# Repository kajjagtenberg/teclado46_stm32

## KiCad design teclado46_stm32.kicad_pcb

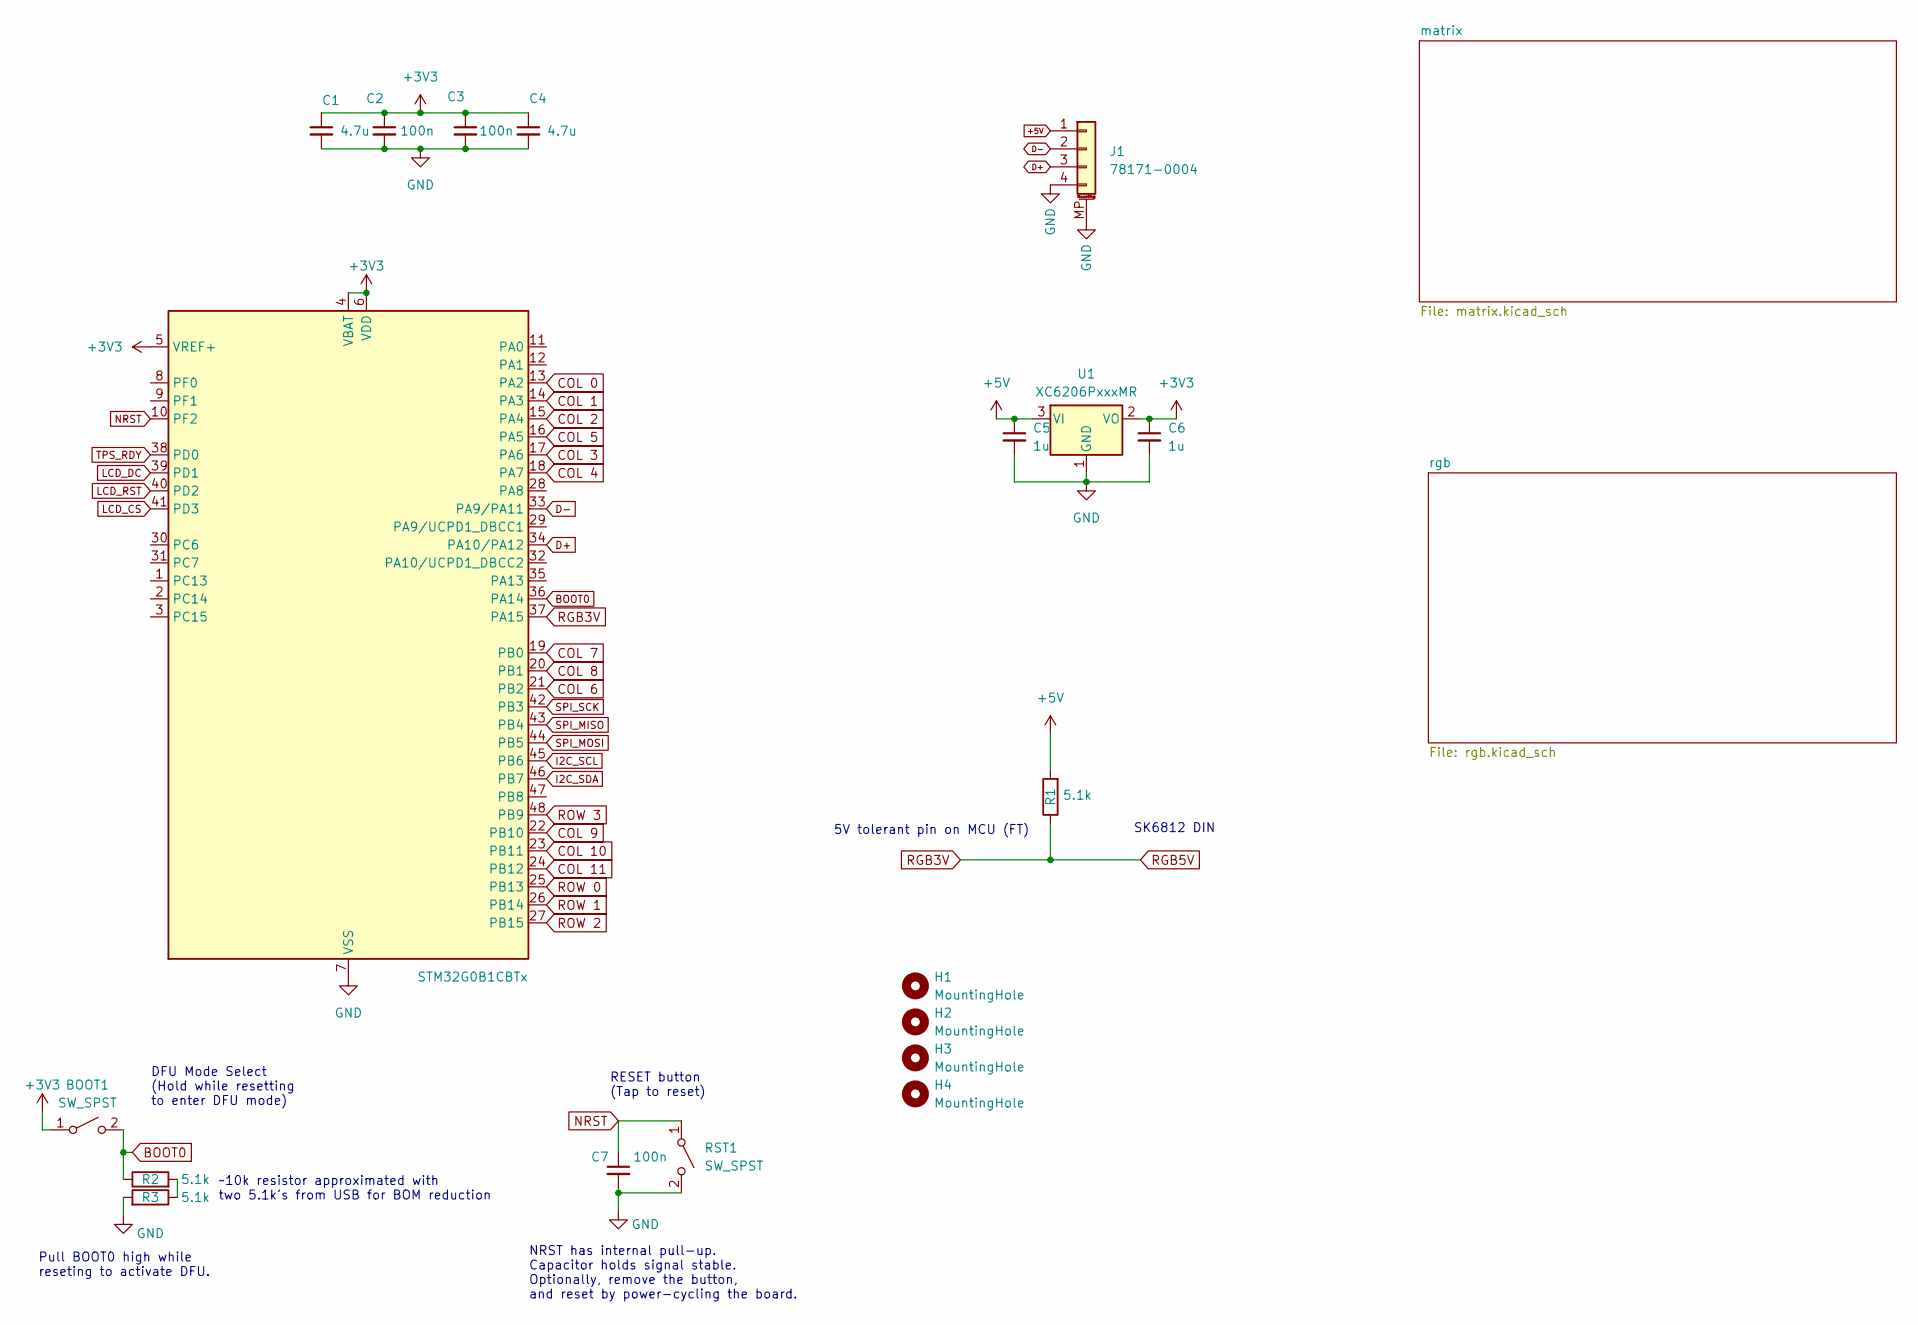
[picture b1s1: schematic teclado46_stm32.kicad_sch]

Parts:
BOOT1: SW_SPST; SW_SPST_TS-1088-xR020; LCSC C720477
C1, C4: 4.7u; C_0402_1005Metric; LCSC C23733
C2, C3, C7: 100n; C_0402_1005Metric; LCSC C1525
C5, C6: 1u; C_0402_1005Metric; LCSC C52923
H1, H2, H3, H4: MountingHole; MountingHole_2.2mm_M2
J1: 78171-0004; Molex_Pico-EZmate_78171-0004_1x04-1MP_P1.20mm_Vertical; Manufacturer Part Number 78171-0004; LCSC C588524
R1, R2, R3: 5.1k; R_0402_1005Metric; LCSC C25905
RST1: SW_SPST; SW_SPST_TS-1088-xR020; LCSC C720477
U1: XC6206PxxxMR; SOT-23-3; LCSC C5446
U2: STM32G0B1CBTx; LQFP-48_7x7mm_P0.5mm; LCSC C2847904

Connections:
+3V3: BOOT1.1 (A), C1.1, C2.1, C3.1, C4.1, C6.1, U1.2 (VO), U2.4 (VBAT), U2.5 (VREF+), U2.6 (VDD)
+5V: C5.1, J1.1, R1.2, U1.3 (VI); also elsewhere on the board
BOOT0: BOOT1.2 (B), R2.1, U2.36 (PA14)
COL 0: U2.13 (PA2); also elsewhere on the board
COL 1: U2.14 (PA3); also elsewhere on the board
COL 2: U2.15 (PA4); also elsewhere on the board
COL 3: U2.17 (PA6); also elsewhere on the board
COL 4: U2.18 (PA7); also elsewhere on the board
COL 5: U2.16 (PA5); also elsewhere on the board
COL 6: U2.21 (PB2); also elsewhere on the board
COL 7: U2.19 (PB0); also elsewhere on the board
COL 8: U2.20 (PB1); also elsewhere on the board
COL 9: U2.22 (PB10); also elsewhere on the board
COL 10: U2.23 (PB11); also elsewhere on the board
COL 11: U2.24 (PB12); also elsewhere on the board
D+: J1.3, U2.34 (PA10/PA12)
D-: J1.2, U2.33 (PA9/PA11)
GND: C1.2, C2.2, C3.2, C4.2, C5.2, C6.2, C7.2, J1.4, J1.MP (MountPin), R3.2, RST1.2 (B), U1.1 (GND), U2.7 (VSS); also elsewhere on the board
I2C_SCL: U2.45 (PB6)
I2C_SDA: U2.46 (PB7)
LCD_CS: U2.41 (PD3)
LCD_DC: U2.39 (PD1)
LCD_RST: U2.40 (PD2)
NRST: C7.1, RST1.1 (A), U2.10 (PF2)
unnamed: R2.2, R3.1
RGB3V: R1.1, U2.37 (PA15); also elsewhere on the board
ROW 0: U2.25 (PB13); also elsewhere on the board
ROW 1: U2.26 (PB14); also elsewhere on the board
ROW 2: U2.27 (PB15); also elsewhere on the board
ROW 3: U2.48 (PB9); also elsewhere on the board
SPI_MISO: U2.43 (PB4)
SPI_MOSI: U2.44 (PB5)
SPI_SCK: U2.42 (PB3)
TPS_RDY: U2.38 (PD0)

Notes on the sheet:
SK6812 DIN
Pull BOOT0 high while reseting to activate DFU.
~10k resistor approximated with two 5.1k's from USB for BOM reduction
DFU Mode Select (Hold while resetting to enter DFU mode)
5V tolerant pin on MCU (FT)
NRST has internal pull-up. Capacitor holds signal stable. Optionally, remove the button, and reset by power-cycling the board.
RESET button (Tap to reset)

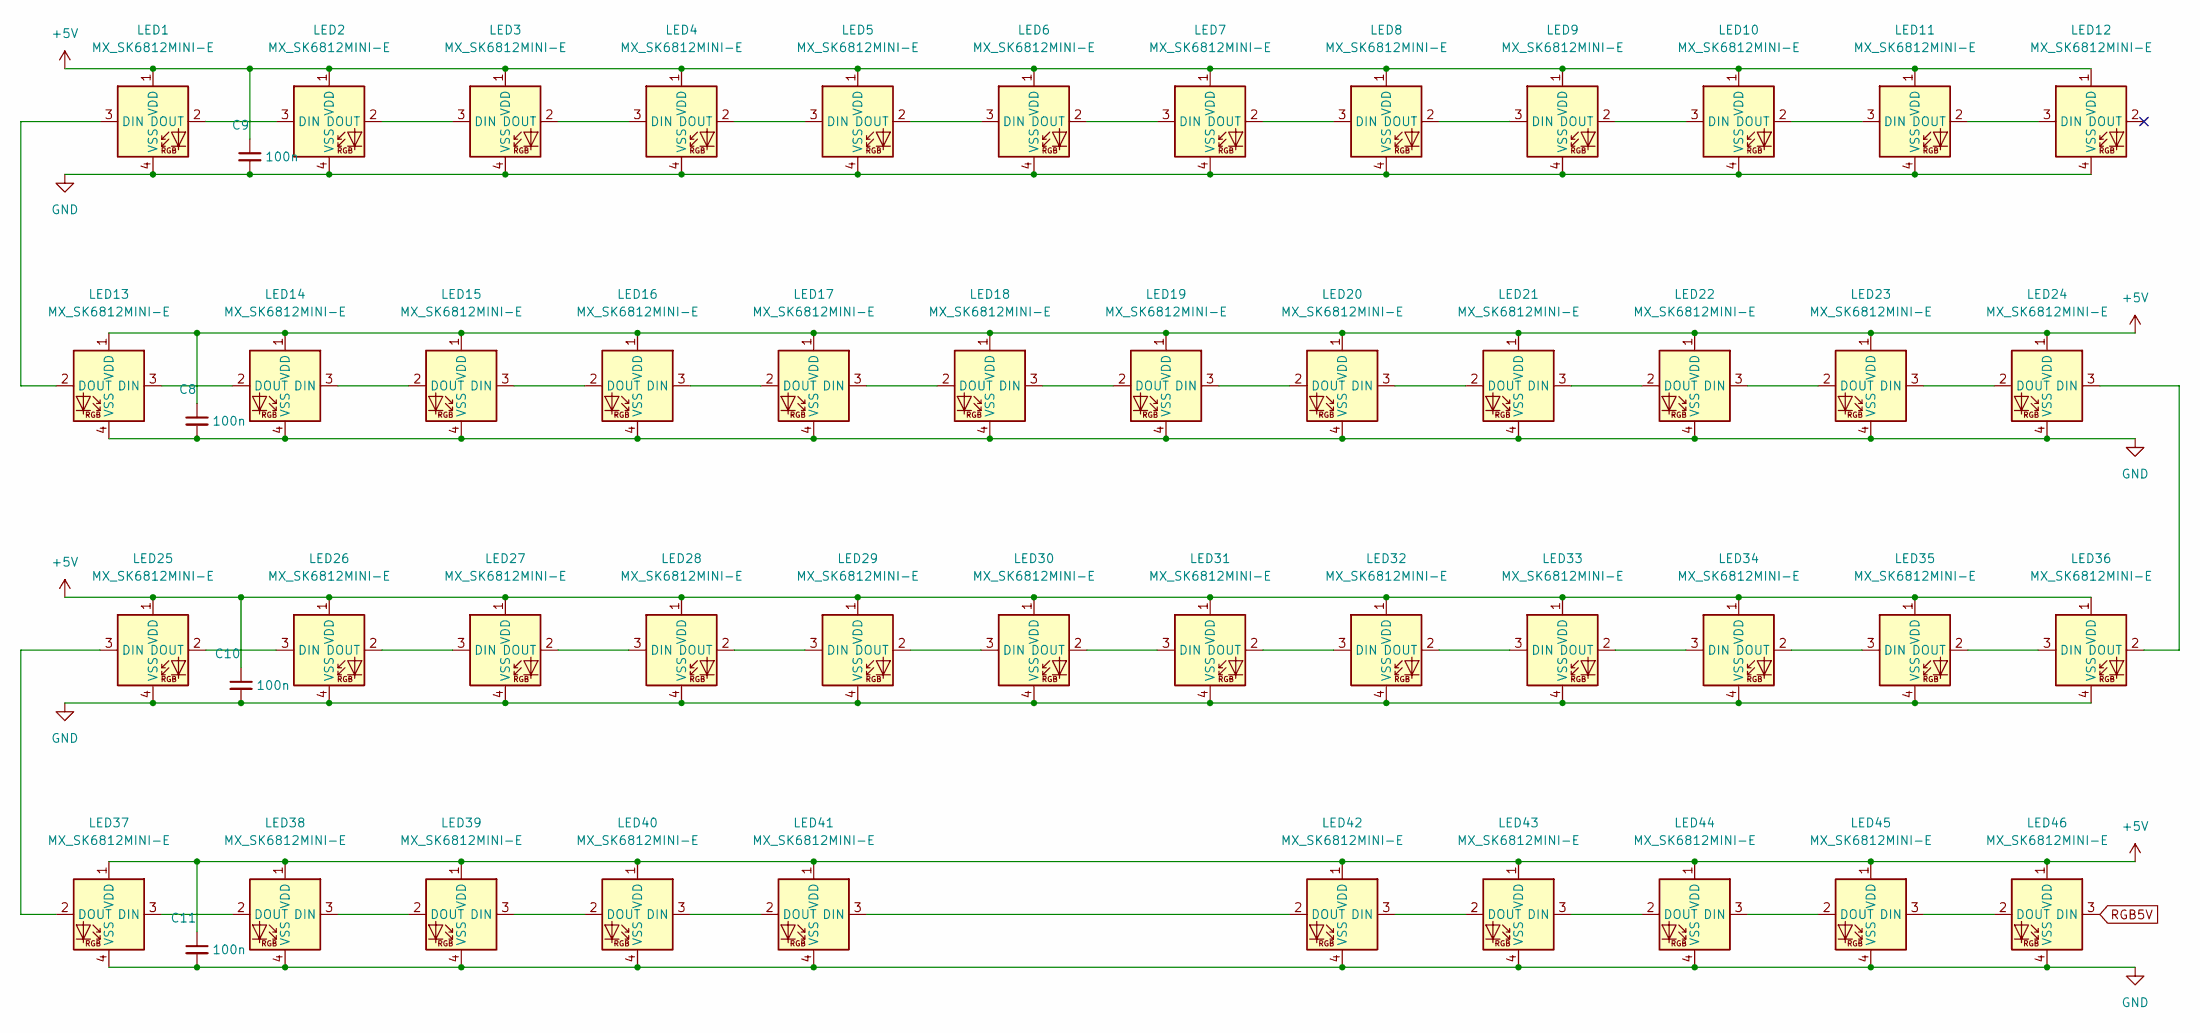
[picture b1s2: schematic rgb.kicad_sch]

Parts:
C8, C9, C10, C11: 100n; C_0402_1005Metric; LCSC C1525
LED1: MX_SK6812MINI-E; LED_MX_6028R-ROT; LCSC C5149201
LED2, LED3, LED4, LED5, LED6, LED7, LED8, LED9, LED10, LED11, LED12, LED25, LED26, LED27, LED28, LED29, LED30, LED31, LED32, LED33, LED34, LED35, LED36: MX_SK6812MINI-E; LED_MX_6028R-ROT
LED13, LED14, LED15, LED16, LED17, LED18, LED19, LED20, LED21, LED22, LED23, LED24, LED37, LED38, LED39, LED40, LED41, LED42, LED43, LED44, LED45, LED46: MX_SK6812MINI-E; LED_MX_6028R

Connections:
+5V: C8.1, C9.1, C10.1, C11.1, LED1.1 (VDD), LED2.1 (VDD), LED3.1 (VDD), LED4.1 (VDD), LED5.1 (VDD), LED6.1 (VDD), LED7.1 (VDD), LED8.1 (VDD), LED9.1 (VDD), LED10.1 (VDD), LED11.1 (VDD), LED12.1 (VDD), LED13.1 (VDD), LED14.1 (VDD), LED15.1 (VDD), LED16.1 (VDD), LED17.1 (VDD), LED18.1 (VDD), LED19.1 (VDD), LED20.1 (VDD), LED21.1 (VDD), LED22.1 (VDD), LED23.1 (VDD), LED24.1 (VDD), LED25.1 (VDD), LED26.1 (VDD), LED27.1 (VDD), LED28.1 (VDD), LED29.1 (VDD), LED30.1 (VDD), LED31.1 (VDD), LED32.1 (VDD), LED33.1 (VDD), LED34.1 (VDD), LED35.1 (VDD), LED36.1 (VDD), LED37.1 (VDD), LED38.1 (VDD), LED39.1 (VDD), LED40.1 (VDD), LED41.1 (VDD), LED42.1 (VDD), LED43.1 (VDD), LED44.1 (VDD), LED45.1 (VDD), LED46.1 (VDD); also elsewhere on the board
GND: C8.2, C9.2, C10.2, C11.2, LED1.4 (VSS), LED2.4 (VSS), LED3.4 (VSS), LED4.4 (VSS), LED5.4 (VSS), LED6.4 (VSS), LED7.4 (VSS), LED8.4 (VSS), LED9.4 (VSS), LED10.4 (VSS), LED11.4 (VSS), LED12.4 (VSS), LED13.4 (VSS), LED14.4 (VSS), LED15.4 (VSS), LED16.4 (VSS), LED17.4 (VSS), LED18.4 (VSS), LED19.4 (VSS), LED20.4 (VSS), LED21.4 (VSS), LED22.4 (VSS), LED23.4 (VSS), LED24.4 (VSS), LED25.4 (VSS), LED26.4 (VSS), LED27.4 (VSS), LED28.4 (VSS), LED29.4 (VSS), LED30.4 (VSS), LED31.4 (VSS), LED32.4 (VSS), LED33.4 (VSS), LED34.4 (VSS), LED35.4 (VSS), LED36.4 (VSS), LED37.4 (VSS), LED38.4 (VSS), LED39.4 (VSS), LED40.4 (VSS), LED41.4 (VSS), LED42.4 (VSS), LED43.4 (VSS), LED44.4 (VSS), LED45.4 (VSS), LED46.4 (VSS); also elsewhere on the board
unnamed: LED1.3 (DIN), LED13.2 (DOUT)
unnamed: LED1.2 (DOUT), LED2.3 (DIN)
unnamed: LED2.2 (DOUT), LED3.3 (DIN)
unnamed: LED3.2 (DOUT), LED4.3 (DIN)
unnamed: LED4.2 (DOUT), LED5.3 (DIN)
unnamed: LED5.2 (DOUT), LED6.3 (DIN)
unnamed: LED6.2 (DOUT), LED7.3 (DIN)
unnamed: LED7.2 (DOUT), LED8.3 (DIN)
unnamed: LED8.2 (DOUT), LED9.3 (DIN)
unnamed: LED9.2 (DOUT), LED10.3 (DIN)
unnamed: LED10.2 (DOUT), LED11.3 (DIN)
unnamed: LED11.2 (DOUT), LED12.3 (DIN)
unnamed: LED13.3 (DIN), LED14.2 (DOUT)
unnamed: LED14.3 (DIN), LED15.2 (DOUT)
unnamed: LED15.3 (DIN), LED16.2 (DOUT)
unnamed: LED16.3 (DIN), LED17.2 (DOUT)
unnamed: LED17.3 (DIN), LED18.2 (DOUT)
unnamed: LED18.3 (DIN), LED19.2 (DOUT)
unnamed: LED19.3 (DIN), LED20.2 (DOUT)
unnamed: LED20.3 (DIN), LED21.2 (DOUT)
unnamed: LED21.3 (DIN), LED22.2 (DOUT)
unnamed: LED22.3 (DIN), LED23.2 (DOUT)
unnamed: LED23.3 (DIN), LED24.2 (DOUT)
unnamed: LED24.3 (DIN), LED36.2 (DOUT)
unnamed: LED25.3 (DIN), LED37.2 (DOUT)
unnamed: LED25.2 (DOUT), LED26.3 (DIN)
unnamed: LED26.2 (DOUT), LED27.3 (DIN)
unnamed: LED27.2 (DOUT), LED28.3 (DIN)
unnamed: LED28.2 (DOUT), LED29.3 (DIN)
unnamed: LED29.2 (DOUT), LED30.3 (DIN)
unnamed: LED30.2 (DOUT), LED31.3 (DIN)
unnamed: LED31.2 (DOUT), LED32.3 (DIN)
unnamed: LED32.2 (DOUT), LED33.3 (DIN)
unnamed: LED33.2 (DOUT), LED34.3 (DIN)
unnamed: LED34.2 (DOUT), LED35.3 (DIN)
unnamed: LED35.2 (DOUT), LED36.3 (DIN)
unnamed: LED37.3 (DIN), LED38.2 (DOUT)
unnamed: LED38.3 (DIN), LED39.2 (DOUT)
unnamed: LED39.3 (DIN), LED40.2 (DOUT)
unnamed: LED40.3 (DIN), LED41.2 (DOUT)
unnamed: LED41.3 (DIN), LED42.2 (DOUT)
unnamed: LED42.3 (DIN), LED43.2 (DOUT)
unnamed: LED43.3 (DIN), LED44.2 (DOUT)
unnamed: LED44.3 (DIN), LED45.2 (DOUT)
unnamed: LED45.3 (DIN), LED46.2 (DOUT)
RGB3V: LED46.3 (DIN); also elsewhere on the board

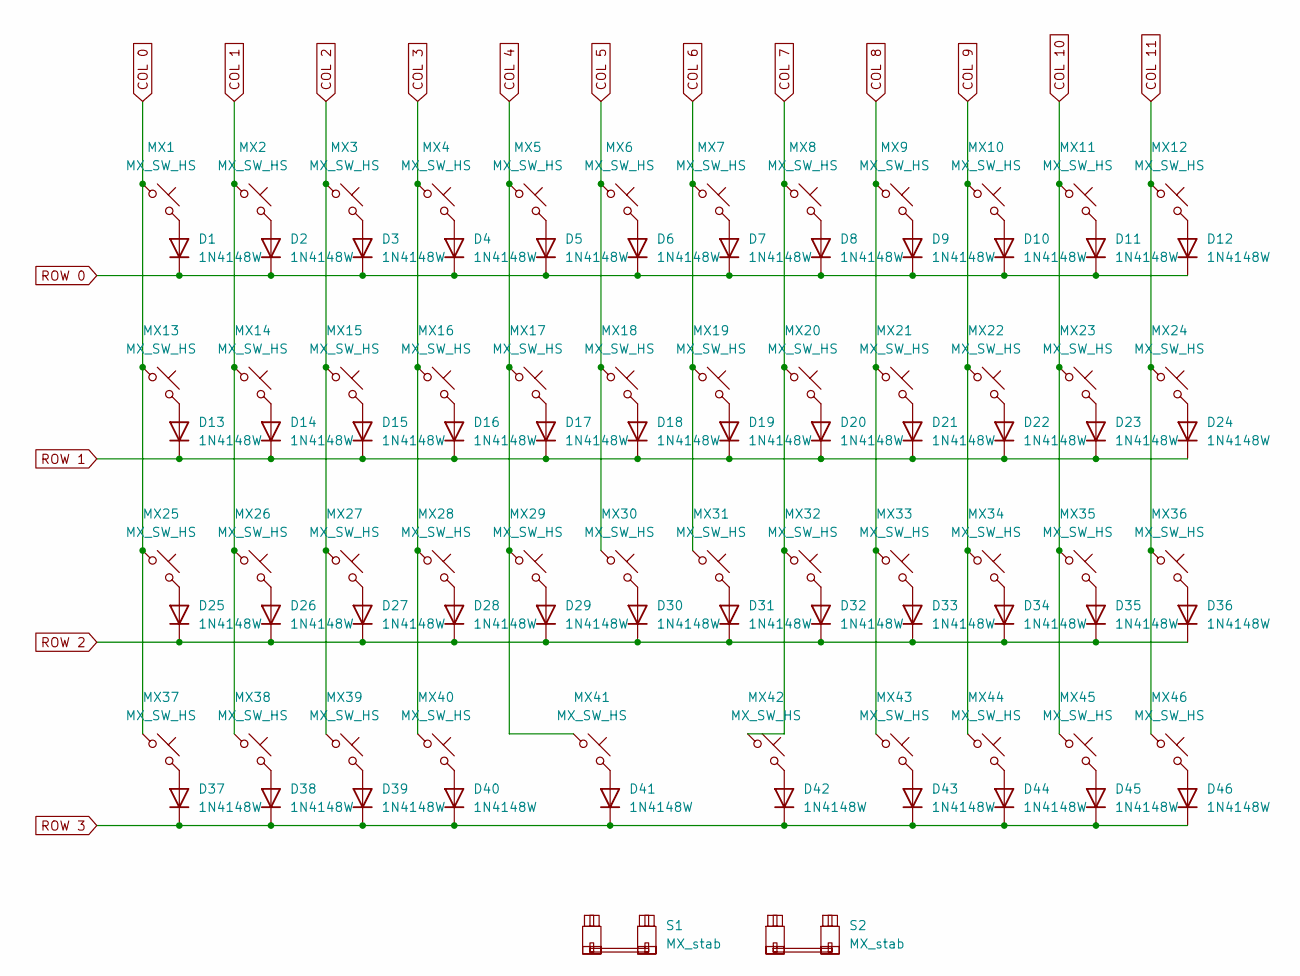
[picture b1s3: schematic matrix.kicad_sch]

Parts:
D1, D2, D3, D4, D5, D6, D7, D8, D9, D10, D11, D12, D13, D14, D15, D16, D17, D18, D19, D20, D21, D22, D23, D24, D25, D26, D27, D28, D29, D30, D31, D32, D33, D34, D35, D36, D37, D38, D39, D40, D41, D42, D43, D44, D45, D46: 1N4148W; D_SOD-123
MX1, MX2, MX3, MX4, MX5, MX6, MX7, MX8, MX9, MX10, MX11, MX12, MX13, MX14, MX15, MX16, MX17, MX18, MX19, MX20, MX21, MX22, MX23, MX24, MX25, MX26, MX27, MX28, MX29, MX30, MX31, MX32, MX33, MX34, MX35, MX36, MX37, MX38, MX39, MX40, MX41, MX42, MX43, MX44, MX45, MX46: MX_SW_HS; SW_MX_HS_CPG151101S11_1u
S1, S2: MX_stab; STAB_MX_P_2u

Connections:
COL 0: MX1.1, MX13.1, MX25.1, MX37.1; also elsewhere on the board
COL 1: MX2.1, MX14.1, MX26.1, MX38.1; also elsewhere on the board
COL 2: MX3.1, MX15.1, MX27.1, MX39.1; also elsewhere on the board
COL 3: MX4.1, MX16.1, MX28.1, MX40.1; also elsewhere on the board
COL 4: MX5.1, MX17.1, MX29.1, MX41.1; also elsewhere on the board
COL 5: MX6.1, MX18.1, MX30.1; also elsewhere on the board
COL 6: MX7.1, MX19.1, MX31.1; also elsewhere on the board
COL 7: MX8.1, MX20.1, MX32.1, MX42.1; also elsewhere on the board
COL 8: MX9.1, MX21.1, MX33.1, MX43.1; also elsewhere on the board
COL 9: MX10.1, MX22.1, MX34.1, MX44.1; also elsewhere on the board
COL 10: MX11.1, MX23.1, MX35.1, MX45.1; also elsewhere on the board
COL 11: MX12.1, MX24.1, MX36.1, MX46.1; also elsewhere on the board
unnamed: D1.2 (A), MX1.2
unnamed: D2.2 (A), MX2.2
unnamed: D3.2 (A), MX3.2
unnamed: D4.2 (A), MX4.2
unnamed: D5.2 (A), MX5.2
unnamed: D6.2 (A), MX6.2
unnamed: D7.2 (A), MX7.2
unnamed: D8.2 (A), MX8.2
unnamed: D9.2 (A), MX9.2
unnamed: D10.2 (A), MX10.2
unnamed: D11.2 (A), MX11.2
unnamed: D12.2 (A), MX12.2
unnamed: D13.2 (A), MX13.2
unnamed: D14.2 (A), MX14.2
unnamed: D15.2 (A), MX15.2
unnamed: D16.2 (A), MX16.2
unnamed: D17.2 (A), MX17.2
unnamed: D18.2 (A), MX18.2
unnamed: D19.2 (A), MX19.2
unnamed: D20.2 (A), MX20.2
unnamed: D21.2 (A), MX21.2
unnamed: D22.2 (A), MX22.2
unnamed: D23.2 (A), MX23.2
unnamed: D24.2 (A), MX24.2
unnamed: D25.2 (A), MX25.2
unnamed: D26.2 (A), MX26.2
unnamed: D27.2 (A), MX27.2
unnamed: D28.2 (A), MX28.2
unnamed: D29.2 (A), MX29.2
unnamed: D30.2 (A), MX30.2
unnamed: D31.2 (A), MX31.2
unnamed: D32.2 (A), MX32.2
unnamed: D33.2 (A), MX33.2
unnamed: D34.2 (A), MX34.2
unnamed: D35.2 (A), MX35.2
unnamed: D36.2 (A), MX36.2
unnamed: D37.2 (A), MX37.2
unnamed: D38.2 (A), MX38.2
unnamed: D39.2 (A), MX39.2
unnamed: D40.2 (A), MX40.2
unnamed: D41.2 (A), MX41.2
unnamed: D42.2 (A), MX42.2
unnamed: D43.2 (A), MX43.2
unnamed: D44.2 (A), MX44.2
unnamed: D45.2 (A), MX45.2
unnamed: D46.2 (A), MX46.2
ROW 0: D1.1 (K), D2.1 (K), D3.1 (K), D4.1 (K), D5.1 (K), D6.1 (K), D7.1 (K), D8.1 (K), D9.1 (K), D10.1 (K), D11.1 (K), D12.1 (K); also elsewhere on the board
ROW 1: D13.1 (K), D14.1 (K), D15.1 (K), D16.1 (K), D17.1 (K), D18.1 (K), D19.1 (K), D20.1 (K), D21.1 (K), D22.1 (K), D23.1 (K), D24.1 (K); also elsewhere on the board
ROW 2: D25.1 (K), D26.1 (K), D27.1 (K), D28.1 (K), D29.1 (K), D30.1 (K), D31.1 (K), D32.1 (K), D33.1 (K), D34.1 (K), D35.1 (K), D36.1 (K); also elsewhere on the board
ROW 3: D37.1 (K), D38.1 (K), D39.1 (K), D40.1 (K), D41.1 (K), D42.1 (K), D43.1 (K), D44.1 (K), D45.1 (K), D46.1 (K); also elsewhere on the board

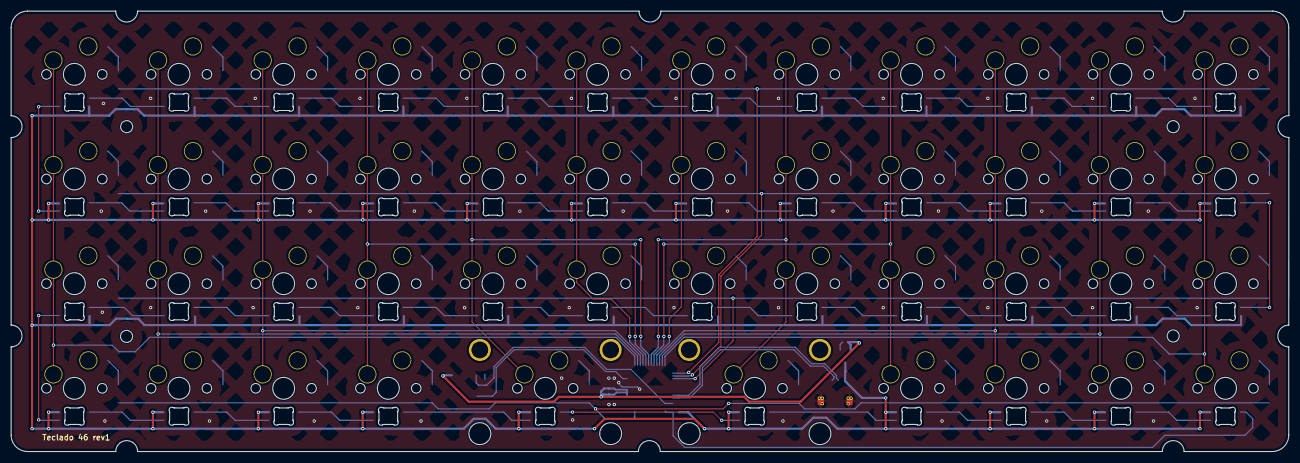
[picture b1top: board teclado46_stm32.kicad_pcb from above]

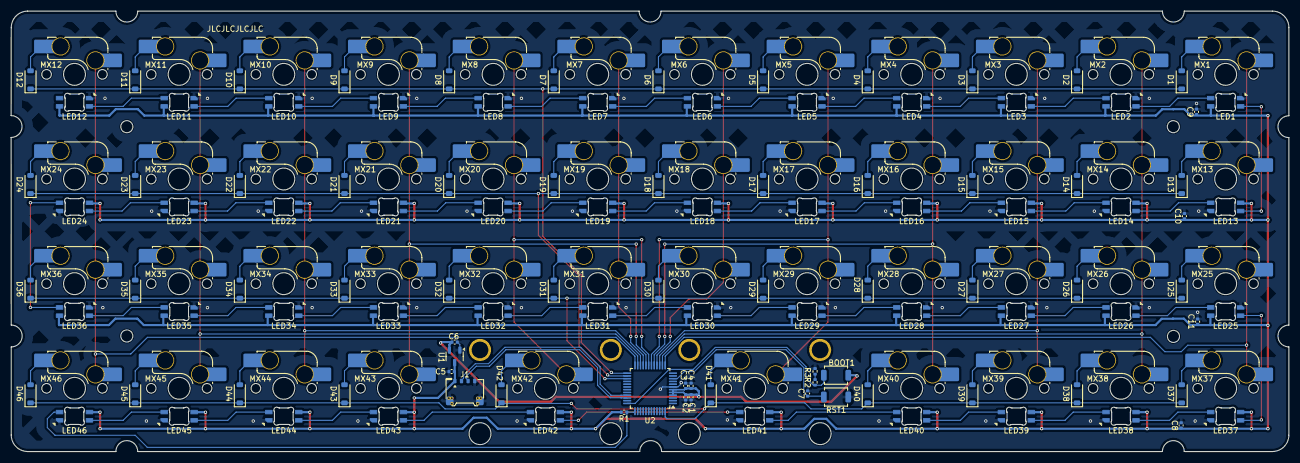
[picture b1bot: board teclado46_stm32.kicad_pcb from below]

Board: 2 copper layers, 232.5 x 80.1 mm, 163 parts (157 on the bottom side), 116 nets.

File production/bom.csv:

Designator,Footprint,Quantity,Value,LCSC Part #
"BOOT1, RST1",SW_SPST_TS-1088-xR020,2,SW_SPST,C720477
"C1, C4",0402,2,4.7u,C23733
"C10, C11, C2, C3, C7, C8, C9",0402,7,100n,C1525
"C5, C6",0402,2,1u,C52923
"D1, D10, D11, D12, D13, D14, D15, D16, D17, D18, D19, D2, D20, D21, D22, D23, D24, D25, D26, D27, D28, D29, D3, D30, D31, D32, D33, D34, D35, D36, D37, D38, D39, D4, D40, D41, D42, D43, D44, D45, D46, D5, D6, D7, D8, D9",D_SOD-123,46,1N4148W,
J1,Molex_Pico-EZmate_78171-0004_1x04-1MP_P1.20mm_Vertical,1,78171-0004,C588524
J2,PinHeader_1x05_P1.00mm_Vertical,1,Conn_01x05,
LED1,LED_MX_6028R-ROT,1,MX_SK6812MINI-E,C5149201
"LED10, LED11, LED12, LED2, LED25, LED26, LED27, LED28, LED29, LED3, LED30, LED31, LED32, LED33, LED34, LED35, LED36, LED4, LED5, LED6, LED7, LED8, LED9",LED_MX_6028R-ROT,23,MX_SK6812MINI-E,
"LED13, LED14, LED15, LED16, LED17, LED18, LED19, LED20, LED21, LED22, LED23, LED24, LED37, LED38, LED39, LED40, LED41, LED42, LED43, LED44, LED45, LED46",LED_MX_6028R,22,MX_SK6812MINI-E,
"MX1, MX10, MX11, MX12, MX13, MX14, MX15, MX16, MX17, MX18, MX19, MX2, MX20, MX21, MX22, MX23, MX24, MX25, MX26, MX27, MX28, MX29, MX3, MX30, MX31, MX32, MX33, MX34, MX35, MX36, MX37, MX38, MX39, MX4, MX40, MX41, MX42, MX43, MX44, MX45, MX46, MX5, MX6, MX7, MX8, MX9",SW_MX_HS_CPG151101S11_1u,46,MX_SW_HS,
"R1, R2, R3",0402,3,5.1k,C25905
"S1, S2",STAB_MX_P_2u,2,MX_stab,
U1,SOT-23-3,1,XC6206PxxxMR,C5446
U2,LQFP-48_7x7mm_P0.5mm,1,STM32G0B1CBTx,C2847904

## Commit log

2025-10-07 chore: init
2025-10-07 chore: label stm32g474
2025-10-07 chore: add stm32g474 datasheet
2025-10-07 chore: add layout
2025-10-07 chore: add keyboard switches
2025-10-07 chore: wired matrix schematic
2025-10-07 chore: routed caps, flash and regulator
2025-10-07 chore: disconnect a Q_CLK and Q_SEL pin
2025-10-07 chore: routed all current components
2025-10-08 chore: add udb connector to schem
2025-10-08 chore: wired udb connector
2025-10-08 chore: routed columns
2025-10-10 chore: routed all columns
2025-10-10 chore: routed rows
2025-10-14 chore: change to g0b1ret6
2025-10-14 chore: add boot0 and nrst
2025-10-14 chore: add led matrix
2025-10-14 chore: set up layout
2025-10-14 chore: routed leds
2025-10-14 chore: routed leds more properly
2025-10-14 chore: routed pre-matrix
2025-10-15 chore: switch to g0b1cbt6
2025-10-15 chore: open-drain for rgb
2025-10-15 chore: routed open-drain
2025-10-15 chore: routed rows and columns
2025-10-15 chore: fix silkscreen
2025-10-15 chore: changed cap footprint
2025-10-15 chore: added lcsc part numbers
2025-10-15 chore: update pcb from schematic
2025-10-16 chore: add mounting holes
2025-10-16 chore: add lifting holes
2025-10-16 chore: removed redundant fill zone
2025-10-16 chore: rerouted 5v line
2025-10-16 chore: cleanup traces and vias
2025-10-16 chore: fixed all errors
2025-10-16 chore: rerouted column
2025-10-16 chore: fixed warnings
2025-10-16 chore: removed unused labels
2025-10-16 chore: rerouted rows
2025-10-16 chore: neater routing
2025-10-16 chore: add decoupling caps for 5v led lines
2025-10-17 chore: improved routing
2025-10-17 chore: changed mcu orientation and rerouted columns
2025-10-17 chore: moved components
2025-10-17 chore: rerouted led din
2025-10-17 chore: updated rbb schema
2025-10-17 chore: fixed errors and warnings
2025-10-17 chore: updated edge cuts
2025-10-17 chore: fixed trace too close to border
2025-10-17 chore: add stabs
2025-10-17 chore: rerouted entire board
2025-10-18 chore: connected to vbat to 3v3
2025-10-18 chore: updated reset and boot button part number
2025-10-18 chore: updated pcb
2025-10-18 chore: add part number for regulator
2025-10-18 chore: add jlcpcb order number silkscreen
2025-10-18 chore: routed decoupling caps together
2025-10-18 chore: rerouted 3v3 caps
2025-10-18 chore: add image to silkscreen
2025-10-18 chore: added more silkscreen
2025-10-18 chore: remove some silkscreen
2025-10-20 chore: add debug header
2025-10-22 chore: production gerber file
